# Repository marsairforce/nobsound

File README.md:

# Nobsound Tube Audio Amplifier Upgrade

I have [This](https://www.amazon.ca/Nobsound-Amplifier-Single-Ended-Handcrafted-Headphone/dp/B073ZXZ3Z5/ref=pd_sbs_23_4/141-4129253-6401105?_encoding=UTF8&pd_rd_i=B073ZXZ3Z5&pd_rd_r=ca6cc800-ad86-41f4-a456-962dbec88bf6&pd_rd_w=sb9mR&pd_rd_wg=G2g7P&pf_rd_p=0ec96c83-1800-4e36-8486-44f5573a2612&pf_rd_r=6QRWN55C83C348ZCCW72&psc=1&refRID=6QRWN55C83C348ZCCW72) audio amplifier.

Specifications:

* Output power: 6.8W * 2
* Frequency response: 20Hz-20KHz
* Input impedance: 100K ohms
* Output impedance: 4/8Ω
* SNR: 90db
* Input Sensitivity: 500mv-2000mv
* Harmonic distortion: 1% (1KHz)
* Tubes
  * 1x 5Z4P
  * 2x 6H8C
  * 4x 6P1
* Operating voltage: 110V
* Weight: about 7 kg
* Size: 260mm x 215mm(including terminals and knobs 260mm) x 150mm (W*D*H)

Chassis is close to the Hammond [1441-22BK3](https://www.hammfg.com/files/parts/pdf/1441-22BK3.pdf)

It worked well for about a year.  But now there are some issues.

## Issues

* The rectifier tube is very noisy with 120Hz. Dynamic microphones anywhere within 1M of this amp pick up the hum when the amp is on. I did not notice or care about the EM radiation before I started using microphones on my desk. For a long time I had terrible hum coming through all my recorded audio. I just thought it was the shitty microphone, or the Art Tube MPC was not very good. But all along, it was the rectifier on my power amp.

* The amplifier gets quite hot. Even the audio transformers are almost too hot to the touch. I expect the tubes to be hot and the power transformer. But there is enough heat that it conducts onto the audio output transformer case. This is too hot I feel to put the amplifier in the shelf on my desk. I currently have it on top of the shelf. That allows heat to rise away from it better. But I would prefer to have it in my shelf and not worry about it lighting up my room. I think the heat is due to the five tubes here. If we had less tubes, there would be less heat. Particularly that rectifier tube.

* Why does a hi-fi audio amplifer even use a rectifier tube. Rectifiers have a lot of internal resistance. This creates a "spongy" effect when there is more demand for power, the output voltage is reduced. This cause compression or or reduced headroom on the output sound. Which is completely not what we want here. This is something perhaps useful in a guitar amplifier right. I think the only reason they used a rectifier tube instead of diodes here is because it looks cool. Or perhaps so they could say "all tube" (so a marketing reason).

* The preamp tube is recently gone bad. I hear terrible crackling on the left speaker. I tested this by swapping the preamp tubes and then had crackling on the right side.

* The balance of the audio is not equal on both sides. I hear a very noticable reduced volume from the left speaker. At first I thought it was the position of the speakers in the room or how I sit relative to the speakers. But I was able to swap the 6P1 tubes and then have a reduced volume output on the right side.

* Retubing this amp is about $200. And that is even when I can find these tubes. The 6H8C preamp tube is about $30 USD. But I can't even find the 6P21 tubes or the 5ZP4 rectifier tube domesically. They are all over Aliexpress. But I am not interesed in ordering (relatively expensive tubes for what they are) and having a long wait time to have them arrive here. I also have less confidence in these Chinese surplus tubes. That they are probably worn in before they were purposed for this amplifer. I don't think I have used my amplifier hard enough to need to replace a bunch of tubes after only one year. They must have been pretty worn out when I got them.

I don’t see the point in having special tubes, when I have a box of 12AX7 tubes and EL84 tubes from guitar amps. Why can't I just make this amplifier use these tubes?
More research,

* The 6H8C tube is basically like a 12AU7.
* The 6P1 is based off the EL90, which is a deficient earlier version of the EL84 tube.
* The 5X4P is just two assemblies of two 1N4005 diodes in series.

## First Wave of Modification

I started this around 2020-07-19 Where I was investigating tube characterstics. I realized, I didn't want to just rewire the tube sockets and hope for the best, but to create a schematic of the amplifier so I can undertand what it going on.

Observable results:

* Fixing the crackling sound from the worn out preamp tube. It is super silent now.
* Fixing the uneven volume levels. Both left and right now appear to have similar volume levels.
* Remove some inefficiencies and heat by replacing rectifier tube with diodes. It does feel like it runs a lot cooler anyway.

It does not look as cool without the bunches of interestingly shaped tubes, but I am hopeful it performs better. I depopulated the other tube sockets (for the 6H8C preamps and rectifier tube) So the old tubes can sit there and look pretty, but are not actually even being lit up.

## Second Wave of Modification

2020-07-24:  I went ahead and ordered all around new electrolytic capacitors from Digikey. I wanted some connectors for playing with Amateur radio stuff, and needed to pad an order to > $100. Waiting over the weekend for the parts to arrive.

2020-07-27: The parts arrived. Installed the new capacitors and re-assembled the amplifier.

## V3 Design

After all that work to put in the sensible auto standby startup circuit, the tubes were still sparking. Even after they were warm. I changed out the tubes. Still having crackling. Even on shutdown.

So there is something horribly wrong here.

It bothers me we have 3 terrible ad-hoc 5V power supplies too. Why do we have that nasty ground loop current draw problem anyway?

Take apart the amp. Gut it completely. Remove the turret board and the tube sockets.

AHA!!! The fucking transformer has center tapped filament supplies! And the center tap is going to ground.  Well that makes sense now why I could not attach a full bridge rectifier with ground reference here. Dammit. How come I didn't see those center tap wires before then?  They are black and cut short and twisted under everything to a ground lug under the standoff to the turret board. I guess I never took this all the way apart before. My schematic did not have the filament center taps on them too. So I was working with incomplete information before.

Doh.

Ok. So this time, going to change the tube sockets. These terrible Chinesium porcelean sockets are likely terrible for the tubes, cracking the pins or not even giving them a good connection. Of course I only have 2 more in stock. I need 4 here. Have to go order them.

Maybe at this point I will design a proper power supply board, for the capacitors and diodes I have. Since I last played with this I have som enice 1KV 1A SMA diodes. and also some nice 400V 8A DPAK diodes. These can be the bridge rectifier for the electronics.

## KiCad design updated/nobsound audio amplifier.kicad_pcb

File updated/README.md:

# Nobsound EL84 Amplifier

This is the updated schematic of the (formerly 6P1) amplifier.

These are likely to change as I continue to hack it up and "improve" it.

## First Wave Enhancemnts

The objective here:

* To replace the 6H8C preamp tube per channel with a 12AX7 tube per channel.
* To replace the pair of 6P1 tubes per channel with a single EL84 tube per channel.
* The rectifier with regular diodes.

### EL84 Power Tubes

So based on the calculations (in the circuit analysis), to use an EL84, I would want the current through the cathode resistor to be about 40mA.  The resistor is 270 ohms, so I am looking for a voltage drop of about V=I*R or 0.04*270 or about 10V.

In practise plugging in an EL84 and testing it out I see it stabilized around 11.75V. Or about 43mA. This is perfect and exactly where we would like it to be.

Reading on https://www.18watt.com/viewtopic.php?t=12875 , the values we have is the values we should use. Ok then.

Wire in the amp and do a test. Well. it seems to work. Let’s do the right channel.
It sounds ok.

I keep reading and finding schematics where the screen resistor should go to the B+, not the output transformer the plate goes to. This amp seems to be wired incorrectly then?

Experiment to wire these to the B+. I only have the 100 ohm screen bypass resistors. I think it should be 1K.
But when I do this, a terrible hum sound and buzzing. Ok, put that back. It might be the hum was because the resistor was 10x too low from what is recommended in this configuration? This is something I would like to understand later.

### Conclusions

By 2020-07-29 I was able meet my original objectives. And to do so without purchasing any electronic components or tubes. Which for me and my projects is highly unusual. And now I have a special sense of smug-ness as well.

I orginally went with a 12AT7 tubes. As they have less gain then the 12AX7 tubes. But I found the sound to be crackly and brittle. I tried to replace the coupling capacitor (which is likely a 0.022uF capacitor) with a 0.1uF capacitor. This gives it a bit more bass response. But still not very good. I guess there is that problem were the 12AT7 is generally considered to be not musical at all. I ended up putting some old Mullard 12AX7 tubes I had in my junk drawer. They have "Holland" printed on them. And even do a really nice vintage filament flash when turning on. But they are really crisp and awesome sounding. Using old tubes (likely liberated from my Traynor amp) onto here is like a fine bottle of wine with peanut butter toast. But you only live once, so might as well enjoy the stuff I have rather than hoarding it forever and not using it.

### Amplifier channel schematic

>R2 and C3 are incorrect here, these go to ground, and are not a feedback as indicated. I later discovered this while updating the schematic on 2020-08-31 for v2.3 revision.

### Power supply schematic

### Updated component list

We added the following parts (to the original schematic)

| Part | Value | Description |
|:--|:--|:--|
| V1 |  | (Removed) |
| V2 | 12AX7 | Left channel preamp tube |
| V3 | EL84 | Left channel power tube |
| V4 | | (Removed) |
| V5 | 12AX7 | Right channel preamp tube |
| V6 | EL84 | Right channel power tube |
| V7 |  | (Removed) |
| C2 | 0.1uF; 450V | (Updated from original schematic) |
| C10 | 0.1uF; 450V | (Updated from original schematic) |
| D5 | 1N4005 | Rectifier board |
| D6 | 1N4005 | Rectifier board |
| D7 | 1N4005 | Rectifier board |
| D8 | 1N4005 | Rectifier board |
| C17 | 47nF; 450V | Rectifier board |
| C18 | 47nF; 450V | Rectifier board |
| C19 | 47NF; 450V | Rectifier board |
| C20 | 47nF; 450V | Rectifier board |
| R21 | 220K; 2 watts | (bleeder resistor I added after C7) |

## Second Wave Enhancements

Some small updates.

* Replaced the electrolytic capacitors with United Chemicon branded capacitors. I have anxiety these capacitors are going to be the cheapest, poorest quality, Chinese made capacitors. Same voltage rating and values (except noted below).

| Part | Value | Old Brand | Notes |
|:-----|:------|:----------|:------|
| C1   | 220uF | Samyoung  | This is now a 1000uF |
| C4   | 100uF | Samyoung  | |
| C5   | 22uF  | Samyoung  | |
| C6   | 150uF | Philips   | |
| C7   | 150uF | Philips   | |
| C8   | 22uF  | Samyoung  | |
| C9   | 100uF | Samyoung  | |
| C12  | 220uF | Samyoung  | This is now a 1000uF |

If they are even the brands they say they are. They could very well be counterfit even.

All I see in the forums is "Replace all Philips caps!!!".

Samyoung is a Korean brand, also known for their terrible quality and reliability.

* Changed the values of the EL84 cathode bypass capacitor from 220uF to 1000uF This is beacuse I have been reading larger capacitor values here help with improving lower frequency responses.
  * https://el34world.com/Forum/index.php?topic=9452.0

I would like to find a more technical calculation for this. So far the sounds do not sound bad. But I can not tell if or how much added bass response I actually have here. I still need to get around to doing a frequency response analysis of this amp.

* Replaced the charred looking 270 ohm resistors with new 270 ohm resistors. Though I ordered 3W kind, I think the old ones may have been 5W. Doh. Well. From the measured voltage and and computed current across this resistor, the power is only about 0.5watts. Though that was idle. I guess we should try to measure the voltage under full load somehow.  For now I will use them and if they burn up, I will replace them with higher power resistors.

## Third Wave Enhancements

The volume knob was all scratchy. I guess the cheap Chinese crap knob that was used just wore out. Funny because I barely even use this knob. And lately I still experience slight imbalance in volume from left to right side. This likely has to do with my room geometry. I would like to have separate volumes for left and right channels.

So had the idea to remove the VU meters (Since those are basically cheap Chinese crap as well and they do not really work for me. They barely deflect on all volumes and I basically never look at them on the amp. So in place of the VU meters to put a potentiometer for the volume control.
I cut a piece of 24ga aluminum I had handy and screwed it inside the chassis using the hardware for the VU meters. Then mounted two 1M pots. The same kind I used in my Traynor amp. They feel very satisfying to touch and turn. Using plastic knobs like I always have used on my amp and before on guitar. They are not ideal but do match the color scheme of black and silver.

I noticed after there was slight buzz on the left channel. Replace the preamp tube. That makde a big difference. I guess the old Holland tube I was using is finally done. Wish I had a kind of tester for tubes. It seems a lot of the way I approach tubes is magic, finding a specific tube works in a specific slot on a chassis.

## 2020-08-31 (v2.3)

* Replace the EL84 cathode bypass resistor (R1, R11) from 270 to 470 ohms. I think it was running a bit too hot before.
* Notice there is no input capacitor to decouple the DC coming in. This is fucking why I get terrible hum when connecting to my Rolls MiniMix and computer audio. Install 0.047uF capacitor in series with inputs.
* Notice there is not Grid stopper resistor into the first stage of the 12AX7 tubes (V2, V5). Install a 4.7K grid stop resistor following the newly added input decoupling capacitor.
* Replace the 12AX7 input grid leak resistor (R5, R10) from 470K to 1M resistor. I think larger value will work better with the newly added decoupling capacitor and grid stopper resistor.
* Notice I had the A/B elements for V2, V5 switched in the schematic from how it is. Update the schematic.
* I had made an error in schematic before, The (C3, C11) actually go to ground, not feedback from 12AX7 output. And (R2, R12) is actually a grid leak resistor for th EL84. Ok. good. I was just about to add one of those.
* There is no grid stopper resistor between preamp output after the capacitor and the EL84. Add a 5.6K resistor.
* Change the EL34 grid leak resistors (R2, R12) from 470K to 1M
* Nicely mount the diode rectifier circuit board onto the inside side of the chassis with standoffs and screws. Before I had this just dangling loose and covered with a piece of tape.

This all came about as I was trying to attach one of those VFD spectum analyzers. It needs 5VDC. I have a 7805 type regulator. Make a rectifier and filter cap and circuit board to connect to the unused 5VAC fillament supply. I see 5V when I test it. And measure 4.9V on the VFD.  Maybe for some reason the VFD requires more current than the regulator IC can supply. I will investigate later.

For now I am excited that these small tunings will make the amp sound a bit less "shrill". It felt there was a bit too much presence or high end sometimes, especially with sounds of people talking.

Since there was no input capacitor, I bet that is why we were having shitty noise when connecting this to the mixer. And why I went on that foxhole to get the Art clean pro. Try to connect the amp directly to the mixer now. Heh. no noise. When crank it up there is the usual high pitch buzz. But that is always there on high gain settings. The hum sound is gone. So I can put away the clean pro box. One less part, and three less cables, on the desk.

## 2020-09-01

Come back to revisit the VFD spectrometer upgrade.

Connect the power supply module I made to a lab power supply. At first I had fun experience of having to whack the power supply to make it work. Cheap Chinese crap strikes again. But it seems the 7805 (or switching regulator version of the one I have) needs at least 9V input to make it turn on. With the loading effect of the VFD anyway.  So with the 5VAC filament this was enough to give me a 5V regulated output on open circuit. But under load this was not enough input voltage.
The total current draw seems to be  about 260mA at 10V input. or 2.6W.

I have one of these small DC-DC converters that takes in 4-9V and then puts out 5V. so let's try this. Hm. The module I have is only 2 watts. That is going to push this pretty hard. Maybe let it run on my desk a bit to see if it burns up after a bit.

It seems to work when I power it off the 5V supply as a clock. But once it starts to work as a display for audio it cuts out and reboots. This means likely that the 5V supply from the transformer can not source enough current here. Try to switch my power supply module to use one of the filament supplies. Ok. that seems to work, and not hose the amp. I bet this is somehow a weak ass counterfit transformer. Maybe I am used to Traynor transformers.

Have the idea to replace the 12AX7 sockets with shielded sockets. I didn't really have a problem with noise. But mounting the VFD spectrograph meter on the chassis in front of the tubes, it is likely I would now be picking up stray  noise from this thing. You can hear the switch supply on it even. The shielded sockets I have are not very good. But they were a lot better than the likely counterfit sockets that were on the chassis. They just fall apart as you take them off.

The VCD appears to work. I mounted it to the chassis with some furniture brackets I had and sheet metal screws. Drill hole to put wires into the chassis. The power supply is inside on the side of the chassis on stand offs. When there is no sound playing there are no bars stuck on a little bit (like I had when I connected this to the output of my computer audio interface, or mixer headphones before). So this allows the clock to turn on. For a while I have been just using this as a clock.

## 2020-09-06

I felt lately the nobsound sounded like i "had a blanket over the speakers". Craking up the master level on the Rolls mixer seems to do less effect than it used to.

Adding that 5.6 k resistor between the preamp and poweramp stages I think. And I don't really need the 4.7K on the input either.

* Go delete R15, R17, R19, R20.

## 2020-10-07 (v2.4)

Replace the 0.22uF capacitor with some not-counterfeit capacitors.  I only had 0.1uF, so putting two of these in parallel.

I think the EL84s are still running a bit too hot.

Also the right and left channels have slightly different volumes for the same knob position.

Measure voltages and resistances. Compute currents.

Experiment with different cathode load resistors for the EL84. I find a 1.2K resistor gives us a good 84% plate dissipation (according to https://robrobinette.com/Tube_Bias_Calculator.htm )

Experiment with a constant current source using transistors. I can only get up to about 40mA on this. I think the voltage drop through the transistors with the high impedance here is losing some of the current?

Experiment with different resistors.

Max cathode current is [65mA](https://en.wikipedia.org/wiki/EL84).

I am getting about 68 to 70mA right now with just the 470 ohm resistor in there.

Find that when I put in the 270 ohm resistor I used to have in there, in series with the 470 ohm (so 740 ohms total) I am able to get about 50mA cathode current.

I like the idea of tinkering with current sources, but to add all this stuff and an adjustment knob when just 2 resistors will work well enough seems silly.

I would use a single resistor. But these are what I have in stock at the moment.

So updating both channels with this series resistor. I now am using about 40-60mA less from the power supply. I think it is no longer doing that high pitch whine from the transformer like it would before. Just the noise from the inverter in the VFD module now.

Put the amp back together for now.

Nope.

It felt a little too much high end now. It is good that it feels more sparkly. Likely less loading the power suppy it is able to do higher frequencies. But it is too bright for my tastes.

* Replace the input bypass capacitors from 0.047uF to 4.7uF. I used SMD ceramics soldered to pin headers, soldered to the wire. Awesome hack.
* Replaced the 2x 0.1uF coupling capacitor between preamp and power amp with a 10uF 250V. its probably fine.
* Added a 330pF 400V bypass cap onto the plate of the preamp. Hoping this helps tame the higher frequencies a bit.

Ok. back together now it sounds better bass response and less of that too much fizzy it was.

## 2021-04-25 (v2.5)

I replaced the EL84 tubes with some new Tungsol tubes. But now I was getting arcing when the tubes were cold.

* Add a soft standby switch - A RC time delay, Schmitt trigger to drive a MOSFET to engage the high voltage to the tubes after they had time to warm up.
* A buffer circuit to drive the VFD to remove some annoying audio bleedover.

I was still getting tube arcing though. These were new tubes. Try some other tubes. Nope still getting arcing.

Measure the voltage across teh tubes. It is way too high. around 390.

Also measure the voltage across the filaments. It is about 6.9V. This is also too high, more than 10% out of spec.

Rip apart the entire amplifier out of anger. The main power transformer is just "too hot".

Discover the filament lines were center tapped. Oh. So that is why I have not been able to add rectifiers to this. Makes sense now. I was fighting the ground reference there in the transformer.  Fucking hell.

Also pissed off at these shit ceramic tube sockets. I think these things are cracking my tubes and causing them to be dead after resocketing them a couple times, as I do for testing. I lost 2 new preamp tubes recently for no reason.

## 2021-05-15

* Order new Belton tube sockets. Install them onto chassis.
* Disconnect the ground reference on the filament windings.
* Use one filament winding to power the bridge rectifier and 5V regulators I have in there for the 5V things, like the display, the soft start circuit, the buffer for the display.
* Experiment with using a full bridge rectifier and [these](https://www.monolithicpower.com/en/mp2307.html) regulators I got from Aliexpress. They say rated up to 3A. I have about 2.34A measured here. Let's try these out.
Build a full bridge rectifier using [SDURD840](https://www.digikey.ca/en/products/detail/smc-diode-solutions/SDURD840TR/6022668) diodes. It is what I had handy.
* In actuality, I am only able to deliver about 4v at 0.5A to the tubes from this regulator module. The load of only 1 tube flattens out its output voltage. This is not anywhere near its rated 3A capacity. I guess this is exactly what I should expect from something I get off Aliexpress, where it is made entirely from counterfeit parts from China.
* Try another [random](https://datasheetgo.com/xl6009e1-datasheet-regulator/) Aliexpress buck converter module I have. This one sais "up to 4A" - Also fail. It can't even drive one tube. There is either some silly short circuit protection here, that these topologies of converters can't power tube filaments. Or these are just crap modules.

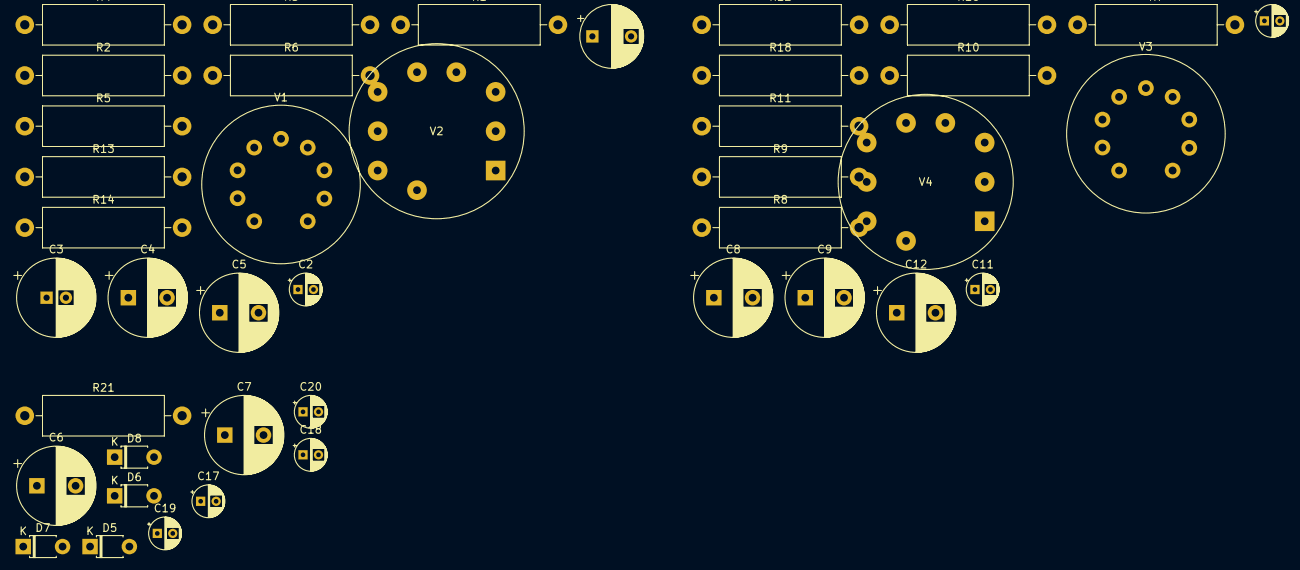
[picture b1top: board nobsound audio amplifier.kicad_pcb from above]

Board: 2 copper layers, 41 parts (0 on the bottom side), 33 nets, no tracks yet.

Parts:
C1: 220uF; CP_Radial_D8.0mm_P5.00mm
C2, C10: 0.1uF; CP_Radial_D4.0mm_P2.00mm
C3: 220K400; CP_Radial_D10.0mm_P2.50mm
C4, C9: 100uF; CP_Radial_D10.0mm_P5.00mm
C5, C8: 22uF; CP_Radial_D10.0mm_P5.00mm
C6, C7: 150uF; CP_Radial_D10.0mm_P5.00mm
C11: 220K400; CP_Radial_D4.0mm_P2.00mm
C12: 220uF; CP_Radial_D10.0mm_P5.00mm
C17, C18, C19, C20: 47nF; CP_Radial_D4.0mm_P2.00mm
D5, D6, D7, D8: 1N4005; D_T-1_P5.08mm_Horizontal
R1, R11: 270; R_Axial_DIN0516_L15.5mm_D5.0mm_P20.32mm_Horizontal
R2, R5, R10, R12: 470K; R_Axial_DIN0516_L15.5mm_D5.0mm_P20.32mm_Horizontal
R3, R8: 2.2K; R_Axial_DIN0516_L15.5mm_D5.0mm_P20.32mm_Horizontal
R4, R9: 30K; R_Axial_DIN0516_L15.5mm_D5.0mm_P20.32mm_Horizontal
R6, R7: 1.5K; R_Axial_DIN0516_L15.5mm_D5.0mm_P20.32mm_Horizontal
R13, R18: 1M; R_Axial_DIN0516_L15.5mm_D5.0mm_P20.32mm_Horizontal
R14, R16: 100; R_Axial_DIN0516_L15.5mm_D5.0mm_P20.32mm_Horizontal
R21: 220K; R_Axial_DIN0516_L15.5mm_D5.0mm_P20.32mm_Horizontal
V1, V3: 12AX7; Valve_ECC-83-1
V2, V4: EL84; Valve_Noval_P

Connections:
/Sheet5F1E3F4C/B+: C7.1, R21.1
/Sheet5F1F04D1/fl1: V1.4, V1.5, V2.5
/Sheet5F1F04D1/fl2: V1.9, V2.4
/Sheet5F200EB8/fl1: V3.4, V3.5, V4.5
/Sheet5F200EB8/fl2: V3.9, V4.4
Earth: C1.2, C4.2, C5.2, C6.2, C7.2, C8.2, C9.2, C12.2, R1.2, R3.2, R5.2, R8.2, R10.2, R11.2, R21.2
unnamed: C1.1, R1.1, V2.3
unnamed: C2.1, R2.1, V2.2
unnamed: C2.2, R4.1, V1.6
unnamed: C3.1, R2.2
unnamed: C3.2, R13.1, V1.7
unnamed: C4.1, R3.1, V1.3
unnamed: C5.1, R4.2, R6.1
unnamed: C8.1, R7.1, R9.2
unnamed: C9.1, R8.1, V3.3
unnamed: C10.1, R12.1, V4.2
unnamed: C10.2, R9.1, V3.6
unnamed: C11.1, R12.2
unnamed: C11.2, R18.1, V3.7
unnamed: C12.1, R11.1, V4.3
unnamed: C17.1, C18.2, D5.1, D6.2
unnamed: C17.2, D5.2
unnamed: C6.1, C18.1, C20.1, D6.1, D8.1
unnamed: C19.1, D7.2
unnamed: C19.2, C20.2, D7.1, D8.2
unnamed: R5.1, V1.2
unnamed: R10.1, V3.2
unnamed: R13.2, V1.1, V1.8
unnamed: R14.1, V2.7
unnamed: R14.2, V2.9
unnamed: R16.1, V4.7
unnamed: R16.2, V4.9
unnamed: R18.2, V3.1, V3.8

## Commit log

2020-07-26 kick off project
    start readme files based on the contents of a google document I started before.
    Schematic file for the original amplifier as well as started an updated schematic. I prefer to keep these separate so I can compare as time goes on.
2020-07-27 finish updated schematic
    Convert tables from google doc to markdown to have these in this repo
2020-07-27 add schematic for updated amp
2020-07-27 install new electrolytic capacitors
2020-08-17 add pictures
2020-09-01 adding some components to try to stop a high pitch squal sound I sometimes hear from the amp
2020-09-01 update documentation
2020-09-01 change EL84 grid leak resistor to 1M
    In the day time, I sort of feel the amp is too quiet. That adding the 5.6k resistor inline has reduced the signal. This small resistance divide is like 98% the input. But that is still the 2% loss of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
2020-09-02 install vfd spectrograph
    upgrade preamp tubes to use shielded sockets.
2020-09-06 remove grid stopped resistors.
2020-10-07 update schematic
    Replaced all the counterfeit capacitor between preamp and power stage. Really opened up the sound.
    Add some pictures
2020-10-08 It didn't sound right to me
    I don't understand how changing the cathode bypass a bit made the amp a lot more brighter. Theory is the power supply was over loaded before and it was not able to drive the high frequency things out?
    Changed more capacitors. Added plate bypass cap to preamp.
    Sounds much better now.
2020-10-14 remove anode bypass capacitors from preamp
2021-04-25 v2.5 modifications
    fix the audio bleedthrough, add soft suspend switch
2021-06-29 updating schematic
